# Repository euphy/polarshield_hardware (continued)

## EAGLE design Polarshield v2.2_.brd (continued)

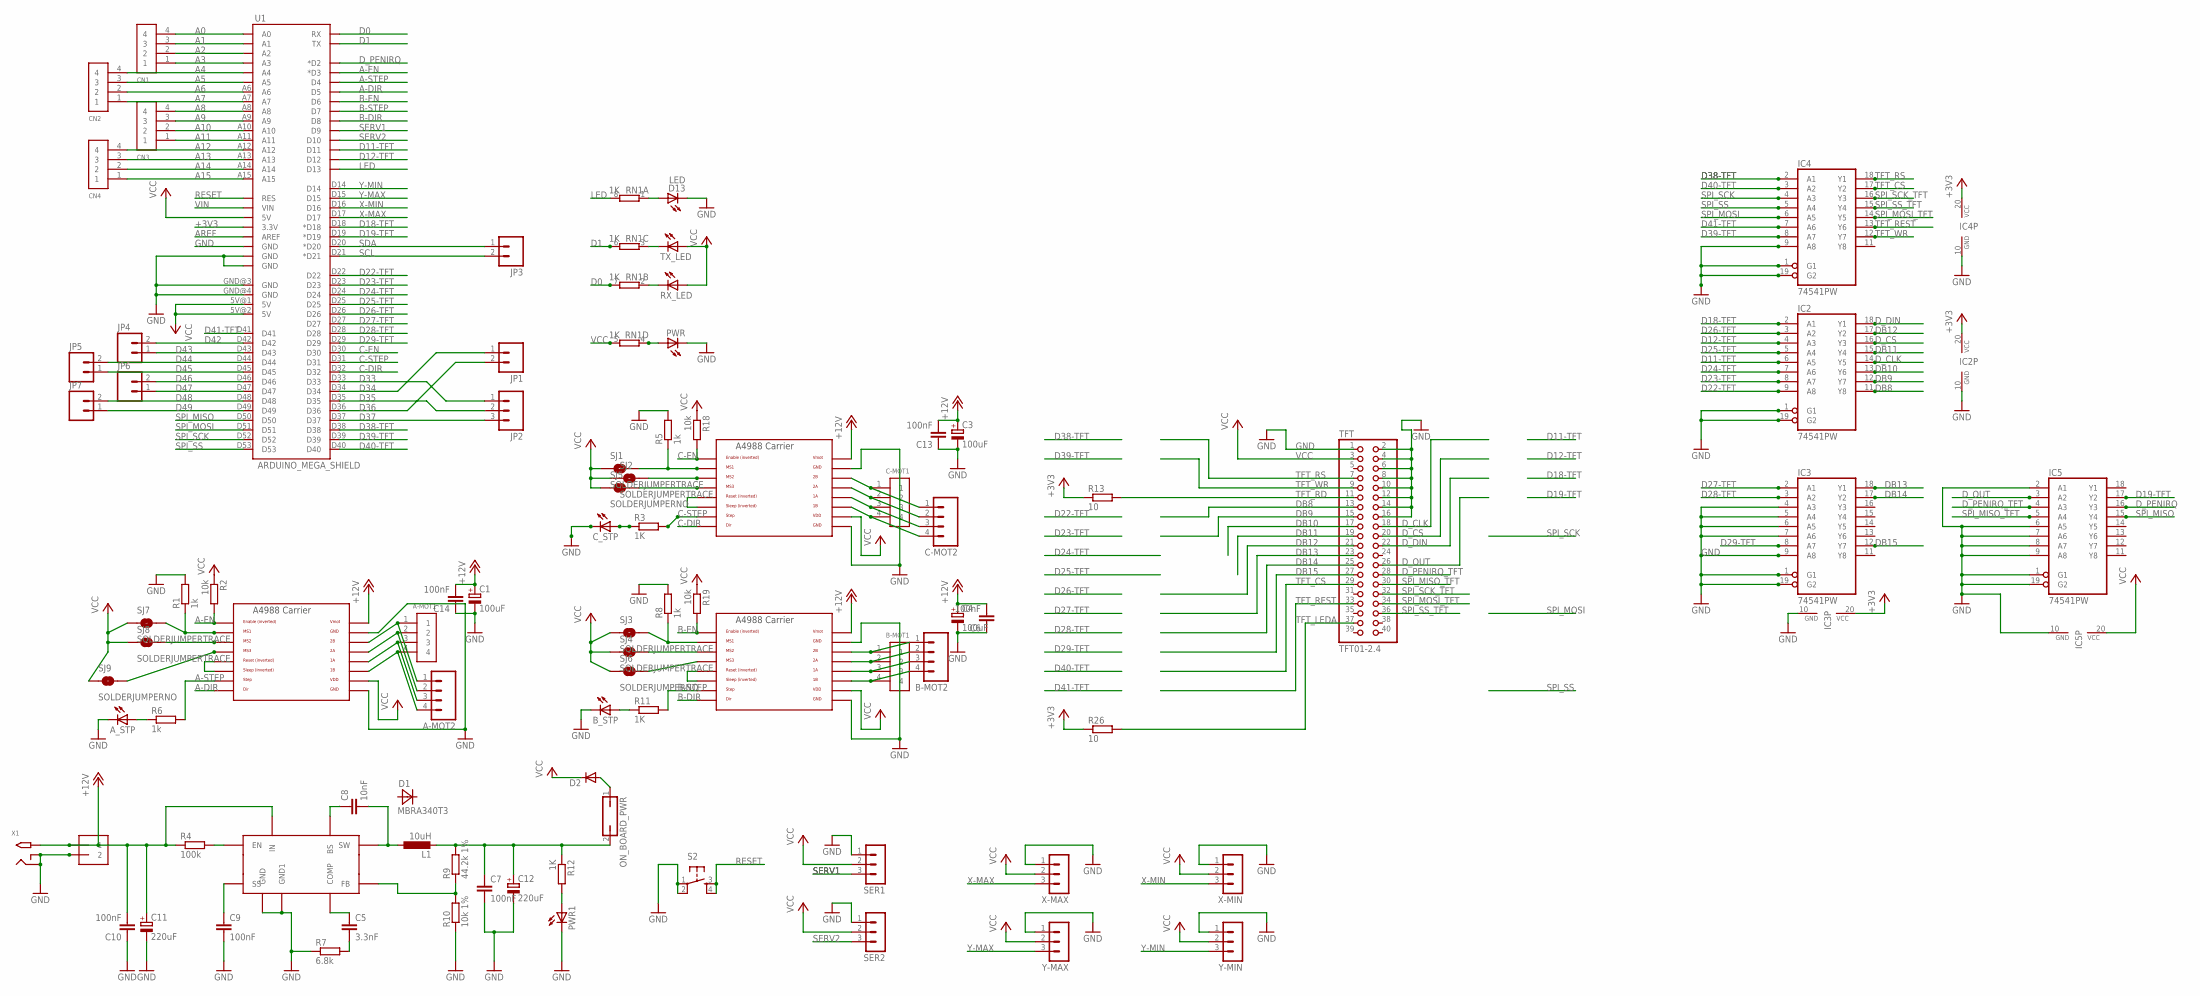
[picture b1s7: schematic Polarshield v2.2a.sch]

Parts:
A-MOT1: 1X4-BIG; 1X04-BIG
A-MOT2: M04SCREW; SCREWTERMINAL-3.5MM-4
A_STP: LEDCHIP-LED0805; CHIP-LED0805
B-MOT1: 1X4-BIG; 1X04-BIG
B-MOT2: M04SCREW; SCREWTERMINAL-3.5MM-4
B_STP: LEDCHIP-LED0805; CHIP-LED0805
C1, C3, C4: 100uF; 153CLV-0605
C5: 3.3nF; C0805K
C6, C13, C14: 100nF; C0805
C7, C9, C10: 100nF; C0805K
C8: 10nF; C0805K
C11, C12: 220uF; 153CLV-0807
C-MOT1: 1X4-BIG; 1X04-BIG
C-MOT2: M04SCREW; SCREWTERMINAL-3.5MM-4
CN1, CN2, CN3, CN4: 1X4-CLEANBIG; 1X04-CLEANBIG
C_STP: LEDCHIP-LED0805; CHIP-LED0805
D1: MBRA340T3; SMA
D2: DIODE-DO214BA; DO214BA
D13: LED; CHIP-LED0805
IC1: MP2307; SOIC8
IC2, IC3, IC4, IC5: 74541PW; TSSOP20
J1: 1X2-3.5MM
JP1, JP3, JP4, JP5, JP6, JP7: M021X02_NO_SILK; 1X02_NO_SILK
JP2: M031X03_NO_SILK; 1X03_NO_SILK
L1: 10uH; PIS2816
ON_BOARD_PWR: JP1Q; JP1
PWR, PWR1: LEDCHIP-LED0805; CHIP-LED0805
R1, R5, R6, R8: 1k; R0805
R2, R18, R19: 10k; R0805
R3, R11, R12: 1K; R0805
R4: 100k; R0805
R7: 6.8k; R0805
R9: 44.2k 1%; R0805
R10: 10k 1%; R0805
R13, R26: 10; R0805
RN1: 1K; EXBS8V
RX_LED: LEDCHIP-LED0805; CHIP-LED0805
S2: TAC_SWITCHPTH; TACTILE-PTH
SER1, SER2: 3PIN-HEADER
SJ1, SJ2, SJ3, SJ4, SJ7, SJ8: SOLDERJUMPERTRACE; SJ_2S-TRACE
SJ5, SJ6, SJ9: SOLDERJUMPERNO; SJ_2S-NO
TFT: TFT01-2.4
TX_LED: LEDCHIP-LED0805; CHIP-LED0805
U1: ARDUINO_MEGA_SHIELD
U$1, U$6, U$7: A4988BREAKOUT
X1: 2.1MMJACKTHM; PJ-102A
X-MAX: 3PIN-HEADER
X-MIN: 3PIN-HEADER
Y-MAX: 3PIN-HEADER
Y-MIN: 3PIN-HEADER

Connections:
+12V: C1.+, C3.+, C4.+, C6.2, C10.2, C11.+, C13.2, C14.2, IC1.IN, J1.1, R4.1, U$1.VMOT, U$6.VMOT, U$7.VMOT, X1.TIP; also elsewhere on the board
A0: CN1.4, U1.A0
A1: CN1.3, U1.A1
A2: CN1.2, U1.A2
A3: CN1.1, U1.A3
A4: CN2.4, U1.A4
A5: CN2.3, U1.A5
A6: CN2.2, U1.A6
A7: CN2.1, U1.A7
A8: CN3.4, U1.A8
A9: CN3.3, U1.A9
A10: CN3.2, U1.A10
A11: CN3.1, U1.A11
A12: CN4.4, U1.A12
A13: CN4.3, U1.A13
A14: CN4.2, U1.A14
A15: CN4.1, U1.A15
A-DIR: U1.D5, U$1.DIR
A-EN: R2.2, U1.D3 (*D3), U$1.EN
A-STEP: R6.2, U1.D4, U$1.STEP
AREF: U1.AREF
B-DIR: U1.D8, U$7.DIR
B-EN: R19.2, U1.D6, U$7.EN
B-STEP: R11.2, U1.D7, U$7.STEP
C-DIR: U1.D32, U$6.DIR
C-EN: R18.2, U1.D30, U$6.EN
C-STEP: R3.2, U1.D31, U$6.STEP
D0: RN1.7 (2), U1.RX
D1: RN1.6 (2), U1.TX
D11-TFT: IC2.6 (A5), U1.D11
D12-TFT: IC2.4 (A3), U1.D12
D19-TFT: IC5.17 (Y2), U1.D19 (*D19); also elsewhere on the board
D22-TFT: IC2.9 (A8), U1.D22
D23-TFT: IC2.8 (A7), U1.D23
D24-TFT: IC2.7 (A6), U1.D24
D25-TFT: IC2.5 (A4), U1.D25
D26-TFT: IC2.3 (A2), U1.D26
D27-TFT: IC3.2 (A1), U1.D27
D28-TFT: IC3.3 (A2), U1.D28
D29-TFT: IC3.8 (A7), U1.D29
D33: JP2.1, U1.D33
D34: JP1.1, U1.D34
D35: JP2.2, U1.D35
D36: JP1.2, U1.D36
D37: JP2.3, U1.D37
D38-TFT: IC4.2 (A1), U1.D38; also elsewhere on the board
D39-TFT: IC4.8 (A7), U1.D39; also elsewhere on the board
D40-TFT: IC4.3 (A2), U1.D40; also elsewhere on the board
D41-TFT: IC4.7 (A6), U1.D41; also elsewhere on the board
D42: JP4.2, U1.D42
D43: JP4.1, U1.D43
D44: JP5.2, U1.D44
D45: JP5.1, U1.D45
D46: JP6.2, U1.D46
D47: JP6.1, U1.D47
D48: JP7.2, U1.D48
D49: JP7.1, U1.D49
DB8: IC2.11 (Y8), TFT.13
DB9: IC2.12 (Y7), TFT.15
DB10: IC2.13 (Y6), TFT.17
DB11: IC2.15 (Y4), TFT.19
DB12: IC2.17 (Y2), TFT.21
DB13: IC3.18 (Y1), TFT.23
DB14: IC3.17 (Y2), TFT.25
DB15: IC3.12 (Y7), TFT.27
D_CLK: IC2.14 (Y5), TFT.18
D_CS: IC2.16 (Y3), TFT.20
D_DIN: IC2.18 (Y1), TFT.22; also elsewhere on the board
D_PENIRQ: IC5.16 (Y3), U1.D2 (*D2); also elsewhere on the board
LED: RN1.8 (2), U1.D13
unnamed: U$6.RST, U$6.SLP (SLEEP)
unnamed: PWR.A, RN1.4 (1)
unnamed: R5.1, SJ1.2, U$6.MS1
unnamed: A-MOT1.1, A-MOT2.1, U$1.2B
unnamed: A-MOT1.2, A-MOT2.2, U$1.2A
unnamed: A-MOT1.3, A-MOT2.3, U$1.1A
unnamed: A-MOT1.4, A-MOT2.4, U$1.1B
unnamed: U$1.RST, U$1.SLP (SLEEP)
unnamed: R1.1, SJ7.2, U$1.MS1
unnamed: SJ2.2, U$6.MS2
unnamed: SJ8.2, U$1.MS2
unnamed: SJ5.2, U$6.MS3
unnamed: U$7.RST, U$7.SLP (SLEEP)
unnamed: SJ9.2, U$1.MS3
unnamed: RN1.2 (1), RX_LED.C
unnamed: RN1.3 (1), TX_LED.C
unnamed: SJ4.2, U$7.MS2
unnamed: B_STP.A, R11.1
unnamed: A_STP.A, R6.1
unnamed: D13.A, RN1.1
unnamed: C-MOT1.1, C-MOT2.1, U$6.2B
unnamed: C-MOT1.2, C-MOT2.2, U$6.2A
unnamed: C_STP.A, R3.1
unnamed: PWR1.A, R12.2
unnamed: C-MOT1.3, C-MOT2.3, U$6.1A
unnamed: C-MOT1.4, C-MOT2.4, U$6.1B
unnamed: B-MOT1.1, B-MOT2.1, U$7.2B
unnamed: B-MOT1.2, B-MOT2.2, U$7.2A
unnamed: B-MOT1.3, B-MOT2.3, U$7.1A
unnamed: SJ6.2, U$7.MS3
unnamed 100: IC1.FB, R9.1, R10.2; also elsewhere on the board
unnamed: R8.1, SJ3.2, U$7.MS1
unnamed 102: IC1.EN, R4.2; also elsewhere on the board
unnamed: B-MOT1.4, B-MOT2.4, U$7.1B
unnamed 105: C9.1, IC1.SS; also elsewhere on the board
unnamed: C5.2, R7.2
unnamed 107: C5.1, IC1.COMP; also elsewhere on the board
unnamed 108: C8.1, IC1.BS; also elsewhere on the board
unnamed 109: C8.2, IC1.SW, L1.1; also elsewhere on the board
RESET: S2.3, S2.4, U1.RES
SCL: JP3.2, U1.D21 (*D21)
SDA: JP3.1, U1.D20 (*D20)
SERV1: SER1.3, U1.D9
SERV2: SER2.3, U1.D10
SPI_MISO: IC5.15 (Y4), U1.D50; also elsewhere on the board
SPI_MOSI: IC4.6 (A5), U1.D51; also elsewhere on the board
SPI_MOSI_TFT: IC4.14 (Y5), TFT.34; also elsewhere on the board
SPI_SCK: IC4.4 (A3), U1.D52; also elsewhere on the board
SPI_SCK_TFT: IC4.16 (Y3), TFT.32; also elsewhere on the board
SPI_SS: IC4.5 (A4), U1.D53; also elsewhere on the board
SPI_SS_TFT: IC4.15 (Y4), TFT.36; also elsewhere on the board
TFT_CS: IC4.17 (Y2), TFT.29; also elsewhere on the board
TFT_LEDA: R26.2, TFT.37
TFT_RD: R13.2, TFT.11
TFT_REST: IC4.13 (Y6), TFT.33; also elsewhere on the board
TFT_RS: IC4.18 (Y1), TFT.7; also elsewhere on the board
TFT_WR: IC4.12 (Y7), TFT.9; also elsewhere on the board
VIN: U1.VIN; also elsewhere on the board
X-MAX: U1.D17, X-MAX.3; also elsewhere on the board
X-MIN: U1.D16, X-MIN.3; also elsewhere on the board
Y-MAX: U1.D15, Y-MAX.3; also elsewhere on the board
Y-MIN: U1.D14, Y-MIN.3; also elsewhere on the board

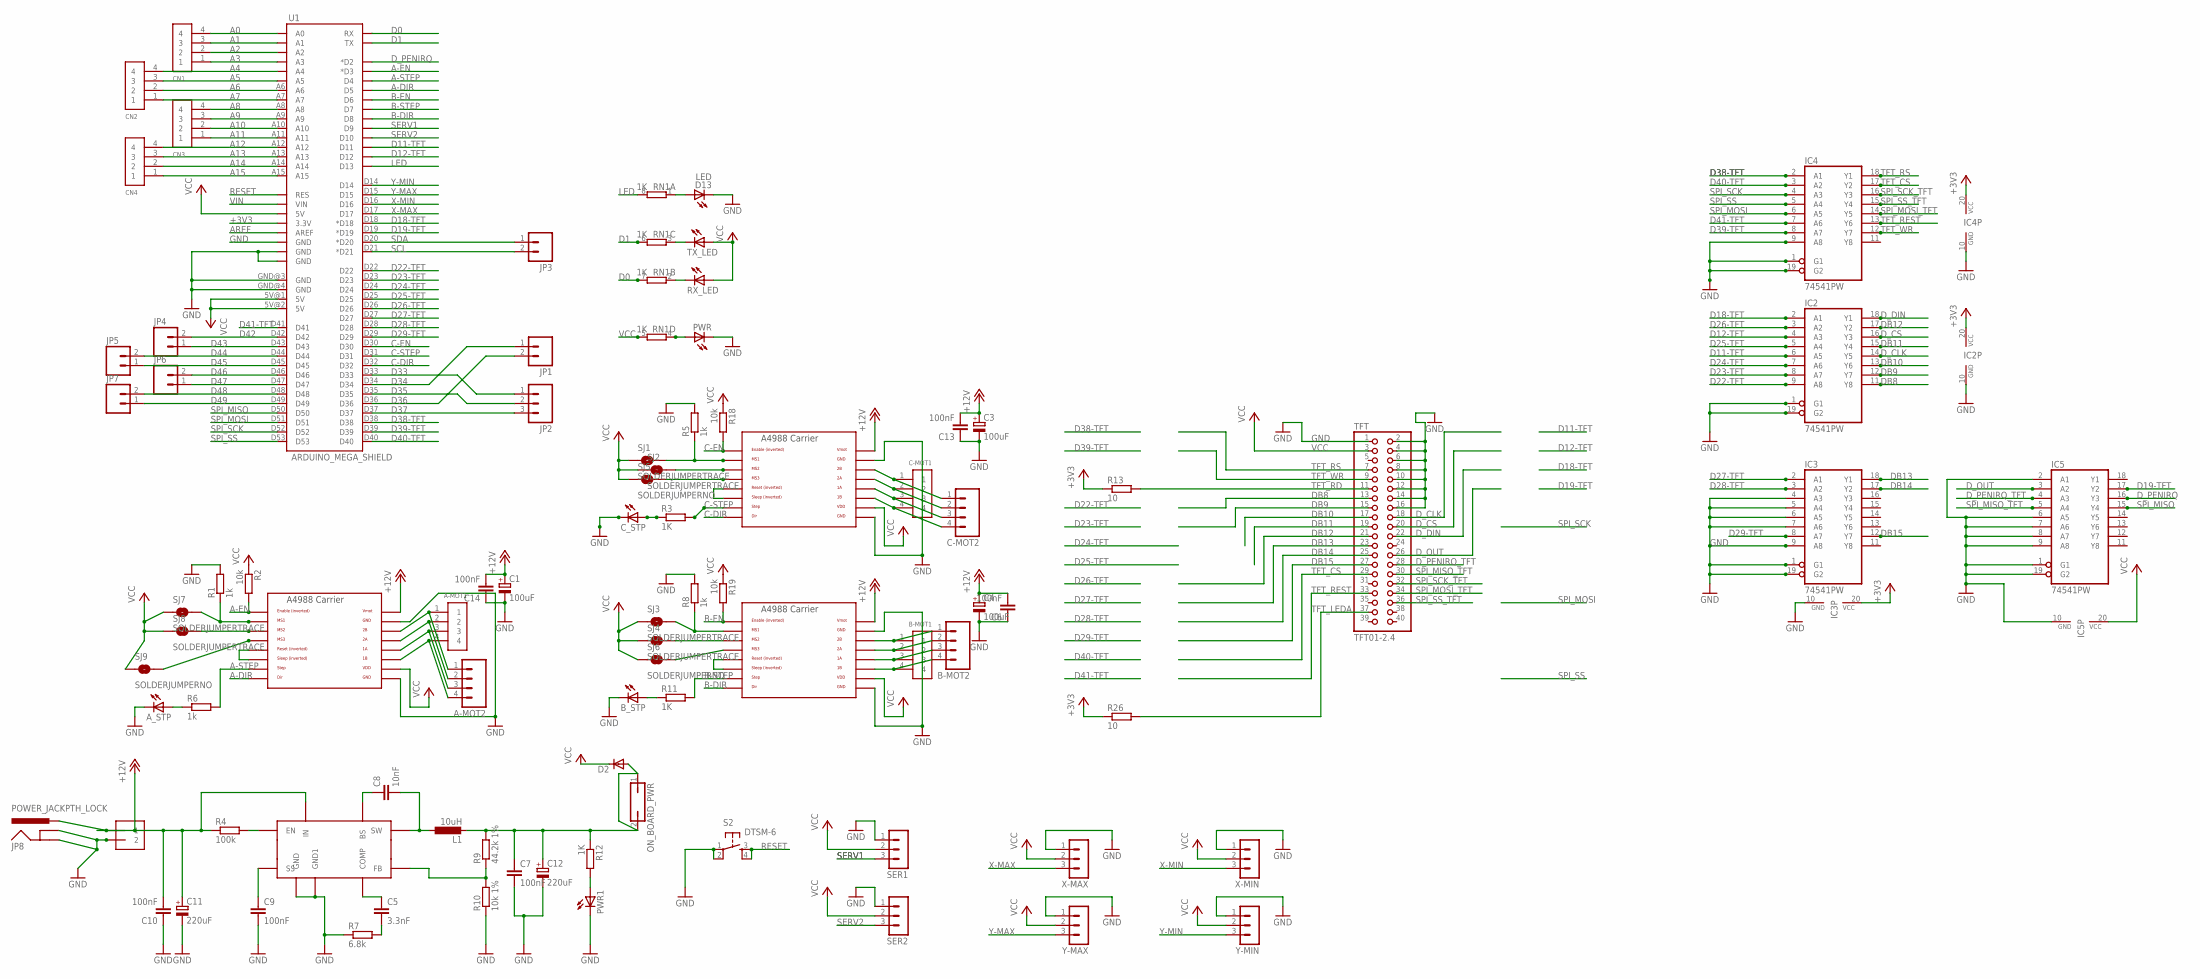
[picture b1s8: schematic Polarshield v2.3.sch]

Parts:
A-MOT1: 1X4-BIG; 1X04-BIG
A-MOT2: M04SCREW; SCREWTERMINAL-3.5MM-4
A_STP: LEDCHIP-LED0805; CHIP-LED0805
B-MOT1: 1X4-BIG; 1X04-BIG
B-MOT2: M04SCREW; SCREWTERMINAL-3.5MM-4
B_STP: LEDCHIP-LED0805; CHIP-LED0805
C1, C3, C4: 100uF; 153CLV-0605
C5: 3.3nF; C0805K
C6, C13, C14: 100nF; C0805
C7, C9, C10: 100nF; C0805K
C8: 10nF; C0805K
C11, C12: 220uF; 153CLV-0807
C-MOT1: 1X4-BIG; 1X04-BIG
C-MOT2: M04SCREW; SCREWTERMINAL-3.5MM-4
CN1, CN2, CN3, CN4: 1X4-CLEANBIG; 1X04-CLEANBIG
C_STP: LEDCHIP-LED0805; CHIP-LED0805
D2: DIODE-DO214BA; DO214BA
D13: LED; CHIP-LED0805
IC1: MP2307; SOIC8
IC2, IC3, IC4, IC5: 74541PW; TSSOP20
J1: 1X2-3.5MM
JP1, JP3, JP4, JP5, JP6, JP7: M021X02_NO_SILK; 1X02_NO_SILK
JP2: M031X03_NO_SILK; 1X03_NO_SILK
JP8: POWER_JACKPTH_LOCK; POWER_JACK_PTH_LOCK
L1: 10uH; PIS2816
ON_BOARD_PWR: JP1Q; JP1
PWR, PWR1: LEDCHIP-LED0805; CHIP-LED0805
R1, R5, R6, R8: 1k; R0805
R2, R18, R19: 10k; R0805
R3, R11, R12: 1K; R0805
R4: 100k; R0805
R7: 6.8k; R0805
R9: 44.2k 1%; R0805
R10: 10k 1%; R0805
R13, R26: 10; R0805
RN1: 1K; EXBS8V
RX_LED: LEDCHIP-LED0805; CHIP-LED0805
S2: DTSM-6
SER1, SER2: 3PIN-HEADER
SJ1, SJ2, SJ3, SJ4, SJ7, SJ8: SOLDERJUMPERTRACE; SJ_2S-TRACE
SJ5, SJ6, SJ9: SOLDERJUMPERNO; SJ_2S-NO
TFT: TFT01-2.4
TX_LED: LEDCHIP-LED0805; CHIP-LED0805
U1: ARDUINO_MEGA_SHIELD
U$1, U$6, U$7: A4988BREAKOUT
X-MAX: 3PIN-HEADER
X-MIN: 3PIN-HEADER
Y-MAX: 3PIN-HEADER
Y-MIN: 3PIN-HEADER

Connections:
+12V: C1.+, C3.+, C4.+, C6.2, C10.2, C11.+, C13.2, C14.2, IC1.IN, J1.1, JP8.PWR, R4.1, U$1.VMOT, U$6.VMOT, U$7.VMOT; also elsewhere on the board
A0: CN1.4, U1.A0
A1: CN1.3, U1.A1
A2: CN1.2, U1.A2
A3: CN1.1, U1.A3
A4: CN2.4, U1.A4
A5: CN2.3, U1.A5
A6: CN2.2, U1.A6
A7: CN2.1, U1.A7
A8: CN3.4, U1.A8
A9: CN3.3, U1.A9
A10: CN3.2, U1.A10
A11: CN3.1, U1.A11
A12: CN4.4, U1.A12
A13: CN4.3, U1.A13
A14: CN4.2, U1.A14
A15: CN4.1, U1.A15
A-DIR: U1.D5, U$1.DIR
A-EN: R2.2, U1.D3 (*D3), U$1.EN
A-STEP: R6.2, U1.D4, U$1.STEP
AREF: U1.AREF
B-DIR: U1.D8, U$7.DIR
B-EN: R19.2, U1.D6, U$7.EN
B-STEP: R11.2, U1.D7, U$7.STEP
C-DIR: U1.D32, U$6.DIR
C-EN: R18.2, U1.D30, U$6.EN
C-STEP: R3.2, U1.D31, U$6.STEP
D0: RN1.7 (2), U1.RX
D1: RN1.6 (2), U1.TX
D11-TFT: IC2.6 (A5), U1.D11
D12-TFT: IC2.4 (A3), U1.D12
D19-TFT: IC5.17 (Y2), U1.D19 (*D19); also elsewhere on the board
D22-TFT: IC2.9 (A8), U1.D22
D23-TFT: IC2.8 (A7), U1.D23
D24-TFT: IC2.7 (A6), U1.D24
D25-TFT: IC2.5 (A4), U1.D25
D26-TFT: IC2.3 (A2), U1.D26
D27-TFT: IC3.2 (A1), U1.D27
D28-TFT: IC3.3 (A2), U1.D28
D29-TFT: IC3.8 (A7), U1.D29
D33: JP2.1, U1.D33
D34: JP1.1, U1.D34
D35: JP2.2, U1.D35
D36: JP1.2, U1.D36
D37: JP2.3, U1.D37
D38-TFT: IC4.2 (A1), U1.D38; also elsewhere on the board
D39-TFT: IC4.8 (A7), U1.D39; also elsewhere on the board
D40-TFT: IC4.3 (A2), U1.D40; also elsewhere on the board
D41-TFT: IC4.7 (A6), U1.D41; also elsewhere on the board
D42: JP4.2, U1.D42
D43: JP4.1, U1.D43
D44: JP5.2, U1.D44
D45: JP5.1, U1.D45
D46: JP6.2, U1.D46
D47: JP6.1, U1.D47
D48: JP7.2, U1.D48
D49: JP7.1, U1.D49
DB8: IC2.11 (Y8), TFT.13
DB9: IC2.12 (Y7), TFT.15
DB10: IC2.13 (Y6), TFT.17
DB11: IC2.15 (Y4), TFT.19
DB12: IC2.17 (Y2), TFT.21
DB13: IC3.18 (Y1), TFT.23
DB14: IC3.17 (Y2), TFT.25
DB15: IC3.12 (Y7), TFT.27
D_CLK: IC2.14 (Y5), TFT.18
D_CS: IC2.16 (Y3), TFT.20
D_DIN: IC2.18 (Y1), TFT.22; also elsewhere on the board
D_PENIRQ: IC5.16 (Y3), U1.D2 (*D2); also elsewhere on the board
LED: RN1.8 (2), U1.D13
unnamed: U$6.RST, U$6.SLP (SLEEP)
unnamed: PWR.A, RN1.4 (1)
unnamed: R5.1, SJ1.2, U$6.MS1
unnamed: A-MOT1.1, A-MOT2.1, U$1.2B
unnamed: A-MOT1.2, A-MOT2.2, U$1.2A
unnamed: A-MOT1.3, A-MOT2.3, U$1.1A
unnamed: A-MOT1.4, A-MOT2.4, U$1.1B
unnamed: U$1.RST, U$1.SLP (SLEEP)
unnamed: R1.1, SJ7.2, U$1.MS1
unnamed: SJ2.2, U$6.MS2
unnamed: SJ8.2, U$1.MS2
unnamed: SJ5.2, U$6.MS3
unnamed: U$7.RST, U$7.SLP (SLEEP)
unnamed: SJ9.2, U$1.MS3
unnamed: RN1.2 (1), RX_LED.C
unnamed: RN1.3 (1), TX_LED.C
unnamed: SJ4.2, U$7.MS2
unnamed: B_STP.A, R11.1
unnamed: A_STP.A, R6.1
unnamed: D13.A, RN1.1
unnamed: C-MOT1.1, C-MOT2.1, U$6.2B
unnamed: C-MOT1.2, C-MOT2.2, U$6.2A
unnamed: C_STP.A, R3.1
unnamed: PWR1.A, R12.2
unnamed: C-MOT1.3, C-MOT2.3, U$6.1A
unnamed: C-MOT1.4, C-MOT2.4, U$6.1B
unnamed: B-MOT1.1, B-MOT2.1, U$7.2B
unnamed: B-MOT1.2, B-MOT2.2, U$7.2A
unnamed: B-MOT1.3, B-MOT2.3, U$7.1A
unnamed: SJ6.2, U$7.MS3
unnamed 100: IC1.FB, R9.1, R10.2; also elsewhere on the board
unnamed: R8.1, SJ3.2, U$7.MS1
unnamed 102: IC1.EN, R4.2; also elsewhere on the board
unnamed: B-MOT1.4, B-MOT2.4, U$7.1B
unnamed 105: C9.1, IC1.SS; also elsewhere on the board
unnamed: C5.2, R7.2
unnamed 107: C5.1, IC1.COMP; also elsewhere on the board
unnamed 108: C8.1, IC1.BS; also elsewhere on the board
unnamed 109: C8.2, IC1.SW, L1.1; also elsewhere on the board
RESET: S2.3, S2.4, U1.RES
SCL: JP3.2, U1.D21 (*D21)
SDA: JP3.1, U1.D20 (*D20)
SERV1: SER1.3, U1.D9
SERV2: SER2.3, U1.D10
SPI_MISO: IC5.15 (Y4), U1.D50; also elsewhere on the board
SPI_MOSI: IC4.6 (A5), U1.D51; also elsewhere on the board
SPI_MOSI_TFT: IC4.14 (Y5), TFT.34; also elsewhere on the board
SPI_SCK: IC4.4 (A3), U1.D52; also elsewhere on the board
SPI_SCK_TFT: IC4.16 (Y3), TFT.32; also elsewhere on the board
SPI_SS: IC4.5 (A4), U1.D53; also elsewhere on the board
SPI_SS_TFT: IC4.15 (Y4), TFT.36; also elsewhere on the board
TFT_CS: IC4.17 (Y2), TFT.29; also elsewhere on the board
TFT_LEDA: R26.2, TFT.37
TFT_RD: R13.2, TFT.11
TFT_REST: IC4.13 (Y6), TFT.33; also elsewhere on the board
TFT_RS: IC4.18 (Y1), TFT.7; also elsewhere on the board
TFT_WR: IC4.12 (Y7), TFT.9; also elsewhere on the board
VIN: U1.VIN; also elsewhere on the board
X-MAX: U1.D17, X-MAX.3; also elsewhere on the board
X-MIN: U1.D16, X-MIN.3; also elsewhere on the board
Y-MAX: U1.D15, Y-MAX.3; also elsewhere on the board
Y-MIN: U1.D14, Y-MIN.3; also elsewhere on the board

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
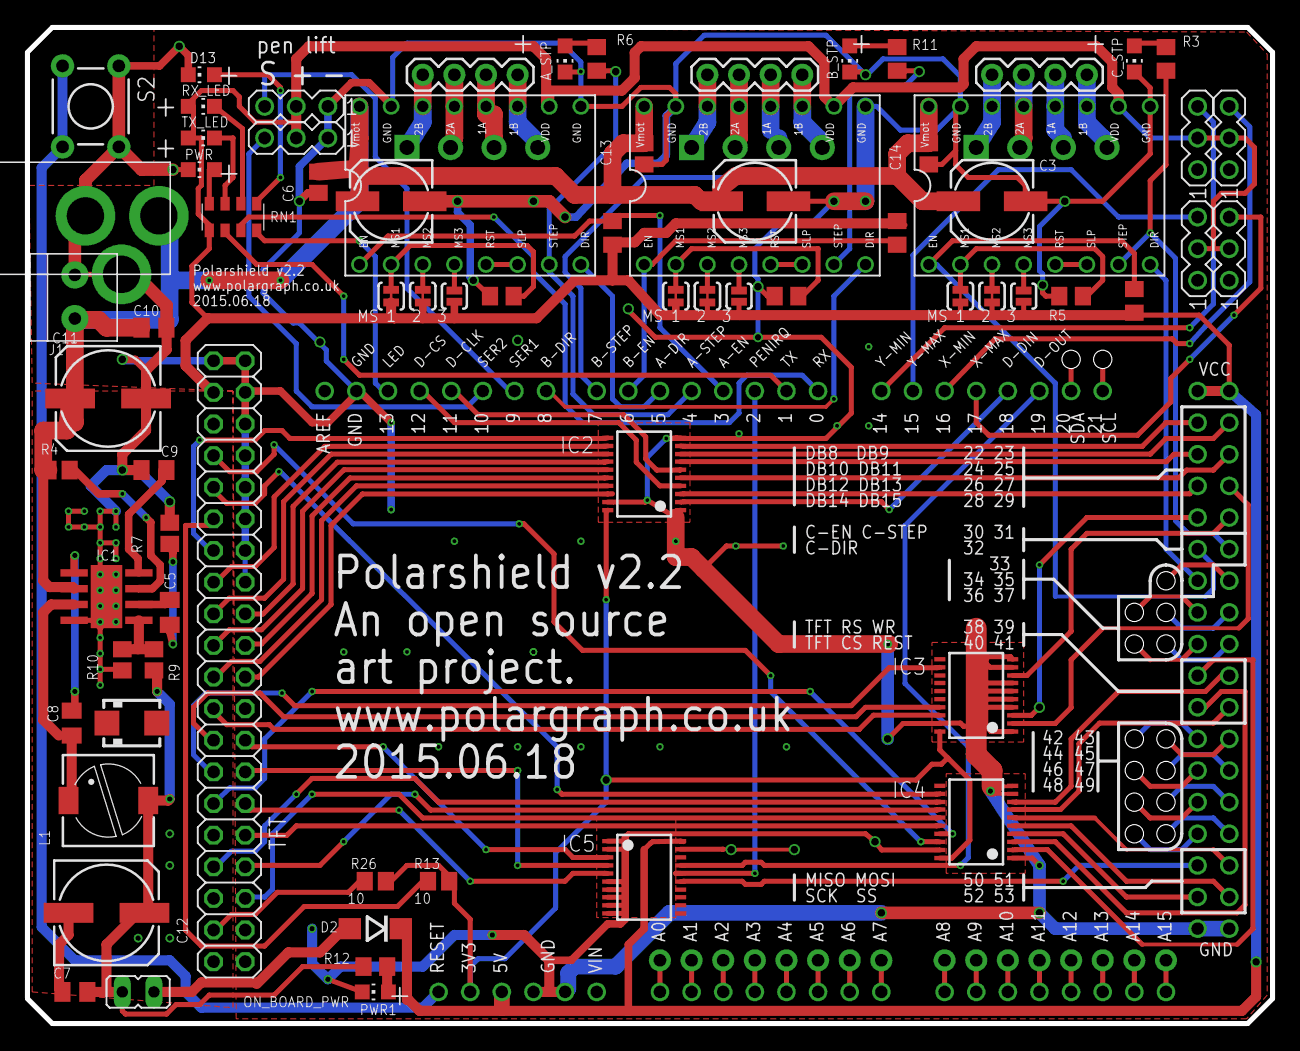
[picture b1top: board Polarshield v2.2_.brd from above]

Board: 4 copper layers, 100.0 x 80.0 mm, 87 parts (0 on the bottom side), 139 nets.

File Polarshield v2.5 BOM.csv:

Part/Designator,Manufacture Part Number/Seeed SKU,Quantity,,value,package,description
"RN1, RN2",301030012,2,,,,Array Chip Resistor
"IC2, IC3, IC4, IC5",74541PW,2,,,TSSOP20,"Octal BUFFER and LINE DRIVER, 3-state"
"C6, C7, C9, C10, C13",C-EUC0805,5,,100nF,C0805,"CAPACITOR, European symbol"
C5,C-EUC0805K,1,,3.3nF,C0805K,"CAPACITOR, European symbol"
C8,C-EUC0805K,1,,10nF,C0805K,"CAPACITOR, European symbol"
"C1, C4",153CLV-0605,2,,100uF,153CLV-0605,"POLARIZED CAPACITOR, European symbol"
"C11, C12",302030053,2,,220uF,153CLV-0807,"POLARIZED CAPACITOR, European symbol"
D2,DIODE-DO214BA,1,,,DO214BA,DIODE
S1,DTSM-6,1,,,DTSM-6,TACTILE BUTTON
"A_STP, B_STP, D13, PWR, PWR1, RX_LED, TX_LED",304090039,7,,yellow,CHIP-LED0805,LED
L1,303010016,1,,1uH,PIS2816,"INDUCTOR, European symbol"
IC1,MP2307,1,,,SOIC8,
"R2, R19",301010299,2,,10k,R0805,"RESISTOR, European symbol"
R4,301010089,1,,100k,R0805,"RESISTOR, European symbol"
R7,301010198,1,,6.8k,R0805,"RESISTOR, European symbol"
R9,R0807,1,,44.2k 1%,R0805,"RESISTOR, European symbol"
R10,301010299,1,,10k 1%,R0805,"RESISTOR, European symbol"
R12,301010311,1,,1K,R0805,"RESISTOR, European symbol"
"R13, R26",301010096,2,,10,R0805,"RESISTOR, European symbol"

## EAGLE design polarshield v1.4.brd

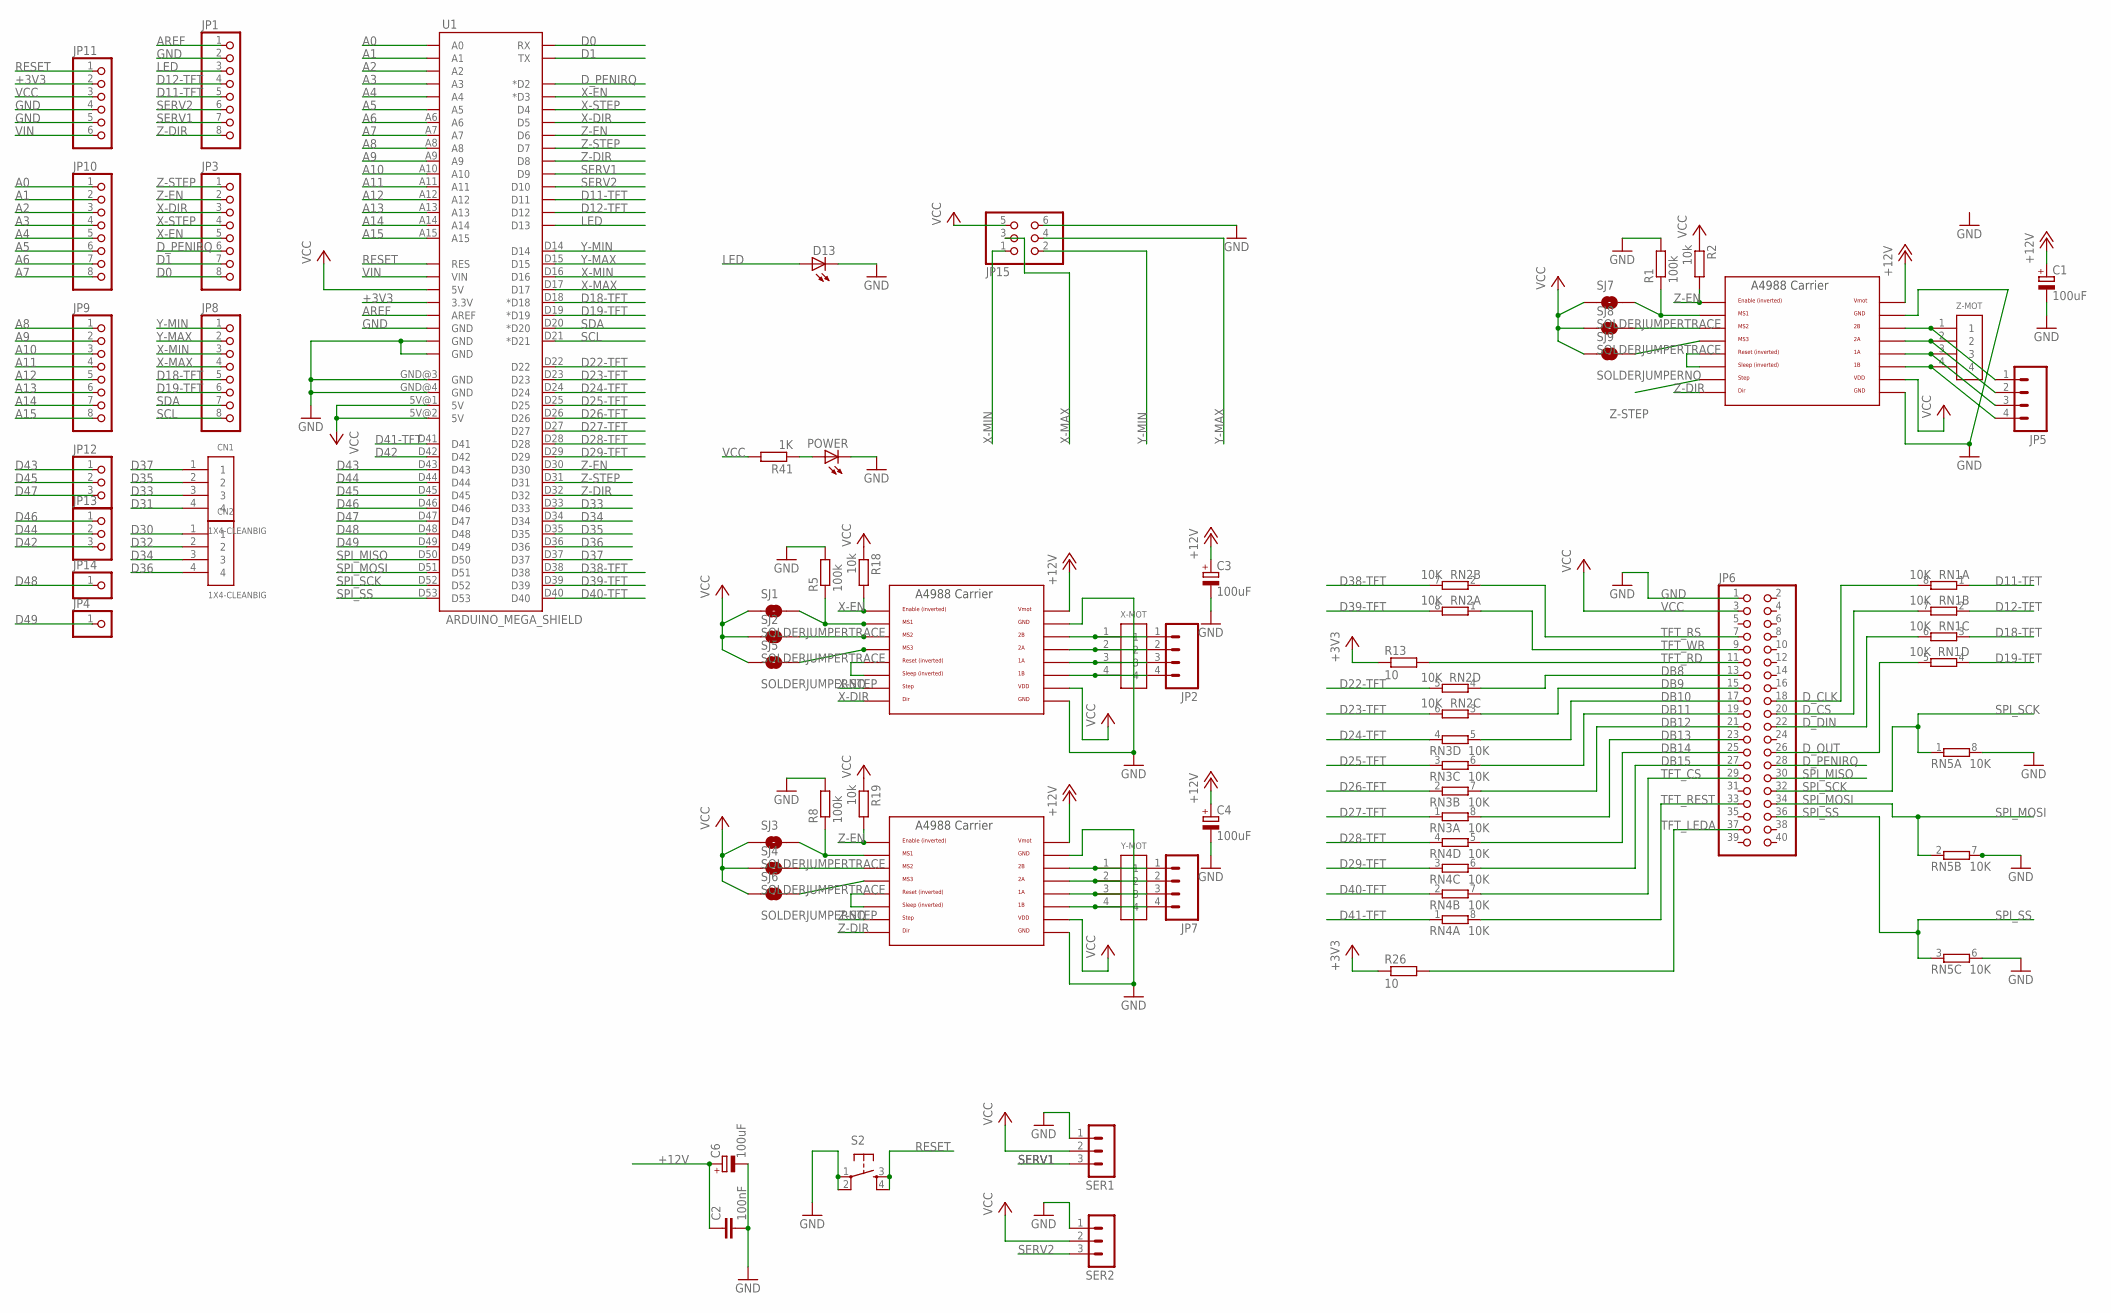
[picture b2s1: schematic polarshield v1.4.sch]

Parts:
C1, C3, C4, C6: 100uF; 153CLV-0605
C2: 100nF; C0805
CN1, CN2: 1X4-CLEANBIG; 1X04-CLEANBIG
D13: LEDCHIP-LED0805; CHIP-LED0805
JP1, JP3, JP8, JP9, JP10: PINHD-1X8CLEANBIG; 1X08-CLEANBIG
JP2, JP5, JP7: M04SCREW; SCREWTERMINAL-3.5MM-4
JP4, JP14: PINHD-1X1CB; 1X01-CLEANBIG
JP6: PINHD-2X20; 2X20
JP11: PINHD-1X6CB; 1X06-CLEANBIG
JP12, JP13: PINHD-1X3CB; 1X03-CLEANBIG
JP15: PINHD-2X3; 2X03
POWER: LEDCHIP-LED0805; CHIP-LED0805
R1, R5, R8: 100k; R0805
R2, R18, R19: 10k; R0805
R13, R26: 10; R0805
R41: 1K; R0805
RN1, RN2, RN3, RN4, RN5: 10K; EXBS8V
S2: TAC_SWITCHPTH; TACTILE-PTH
SER1, SER2: 3PIN-HEADER
SJ1, SJ2, SJ3, SJ4, SJ7, SJ8: SOLDERJUMPERTRACE; SJ_2S-TRACE
SJ5, SJ6, SJ9: SOLDERJUMPERNO; SJ_2S-NO
U1: ARDUINO_MEGA_SHIELD
U$1, U$6, U$7: A4988BREAKOUT
X-MOT: 1X4-BIG; 1X04-BIG
Y-MOT: 1X4-BIG; 1X04-BIG
Z-MOT: 1X4-BIG; 1X04-BIG

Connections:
+3V3: JP11.2, R13.1, R26.1, U1.3.3V
+12V: C1.+, C2.1, C3.+, C4.+, C6.+, U$1.VMOT, U$6.VMOT, U$7.VMOT
A0: JP10.1, U1.A0
A1: JP10.2, U1.A1
A2: JP10.3, U1.A2
A3: JP10.4, U1.A3
A4: JP10.5, U1.A4
A5: JP10.6, U1.A5
A6: JP10.7, U1.A6
A7: JP10.8, U1.A7
A8: JP9.1, U1.A8
A9: JP9.2, U1.A9
A10: JP9.3, U1.A10
A11: JP9.4, U1.A11
A12: JP9.5, U1.A12
A13: JP9.6, U1.A13
A14: JP9.7, U1.A14
A15: JP9.8, U1.A15
AREF: JP1.1, U1.AREF
D0: JP3.8, U1.RX
D1: JP3.7, U1.TX
D11-TFT: JP1.5, RN1.1, U1.D11
D12-TFT: JP1.4, RN1.2 (1), U1.D12
D18-TFT: JP8.5, RN1.3 (1), U1.D18 (*D18)
D19-TFT: JP8.6, RN1.4 (1), U1.D19 (*D19)
D22-TFT: RN2.5 (2), U1.D22
D23-TFT: RN2.6 (2), U1.D23
D24-TFT: RN3.4 (1), U1.D24
D25-TFT: RN3.3 (1), U1.D25
D26-TFT: RN3.2 (1), U1.D26
D27-TFT: RN3.1, U1.D27
D28-TFT: RN4.4 (1), U1.D28
D29-TFT: RN4.3 (1), U1.D29
D30: CN2.1
D31: CN1.4
D32: CN2.2
D33: CN1.3, U1.D33
D34: CN2.3, U1.D34
D35: CN1.2, U1.D35
D36: CN2.4, U1.D36
D37: CN1.1, U1.D37
D38-TFT: RN2.7 (2), U1.D38
D39-TFT: RN2.8 (2), U1.D39
D40-TFT: RN4.2 (1), U1.D40
D41-TFT: RN4.1, U1.D41
D42: JP13.3, U1.D42
D43: JP12.1, U1.D43
D44: JP13.2, U1.D44
D45: JP12.2, U1.D45
D46: JP13.1, U1.D46
D47: JP12.3, U1.D47
D48: JP14.1, U1.D48
D49: JP4.1, U1.D49
DB8: JP6.13, RN2.4 (1)
DB9: JP6.15, RN2.3 (1)
DB10: JP6.17, RN3.5 (2)
DB11: JP6.19, RN3.6 (2)
DB12: JP6.21, RN3.7 (2)
DB13: JP6.23, RN3.8 (2)
DB14: JP6.25, RN4.5 (2)
DB15: JP6.27, RN4.6 (2)
D_CLK: JP6.18, RN1.8 (2)
D_CS: JP6.20, RN1.7 (2)
D_DIN: JP6.22, RN1.6 (2)
D_OUT: JP6.26, RN1.5 (2)
D_PENIRQ: JP3.6, JP6.28, U1.D2 (*D2)
GND: C1.-, C2.2, C3.-, C4.-, C6.-, D13.C, JP1.2, JP6.1, JP11.4, JP11.5, JP15.6, POWER.C, R1.2, R5.2, R8.2, RN5.6 (2), RN5.7 (2), RN5.8 (2), S2.1, S2.2, SER1.1, SER2.1, U1.GND@0 (GND), U1.GND@1 (GND), U1.GND@2 (GND), U1.GND@3 (GND), U1.GND@4 (GND), U$1.GND, U$1.GND@0 (GND), U$6.GND, U$6.GND@0 (GND), U$7.GND, U$7.GND@0 (GND)
LED: D13.A, JP1.3, U1.D13
unnamed: U$6.RST, U$6.SLP (SLEEP)
unnamed: POWER.A, R41.1
unnamed: R5.1, SJ1.2, U$6.MS1
unnamed: SJ8.2, U$1.MS2
unnamed: SJ9.2, U$1.MS3
unnamed: R1.1, SJ7.2, U$1.MS1
unnamed: JP5.1, U$1.2B, Z-MOT.1
unnamed: JP5.2, U$1.2A, Z-MOT.2
unnamed: JP5.3, U$1.1A, Z-MOT.3
unnamed: SJ2.2, U$6.MS2
unnamed: JP5.4, U$1.1B, Z-MOT.4
unnamed: SJ5.2, U$6.MS3
unnamed: U$7.RST, U$7.SLP (SLEEP)
unnamed: U$1.RST, U$1.SLP (SLEEP)
unnamed: SJ4.2, U$7.MS2
unnamed: JP2.1, U$6.2B, X-MOT.1
unnamed: JP2.2, U$6.2A, X-MOT.2
unnamed: JP2.3, U$6.1A, X-MOT.3
unnamed: JP2.4, U$6.1B, X-MOT.4
unnamed: JP7.1, U$7.2B, Y-MOT.1
unnamed: JP7.2, U$7.2A, Y-MOT.2
unnamed: JP7.3, U$7.1A, Y-MOT.3
unnamed: SJ6.2, U$7.MS3
unnamed: R8.1, SJ3.2, U$7.MS1
unnamed: JP7.4, U$7.1B, Y-MOT.4
RESET: JP11.1, S2.3, S2.4, U1.RES
SCL: JP8.8, U1.D21 (*D21)
SDA: JP8.7, U1.D20 (*D20)
SERV1: JP1.7, SER1.3, U1.D9
SERV2: JP1.6, SER2.3, U1.D10
SPI_MISO: JP6.30, U1.D50
SPI_MOSI: JP6.34, RN5.2 (1), U1.D51
SPI_SCK: JP6.32, RN5.1, U1.D52
SPI_SS: JP6.36, RN5.3 (1), U1.D53
TFT_CS: JP6.29, RN4.7 (2)
TFT_LEDA: JP6.37, R26.2
TFT_RD: JP6.11, R13.2
TFT_REST: JP6.33, RN4.8 (2)
TFT_RS: JP6.7, RN2.2 (1)
TFT_WR: JP6.9, RN2.1
VCC: JP6.3, JP11.3, JP15.5, R2.1, R18.1, R19.1, R41.2, SER1.2, SER2.2, SJ1.1, SJ2.1, SJ3.1, SJ4.1, SJ5.1, SJ6.1, SJ7.1, SJ8.1, SJ9.1, U1.5V@0 (5V), U1.5V@1 (5V), U1.5V@2 (5V), U$1.VDD, U$6.VDD, U$7.VDD
VIN: JP11.6, U1.VIN
X-DIR: JP3.3, U1.D5, U$6.DIR
X-EN: JP3.5, R18.2, U1.D3 (*D3), U$6.EN
X-MAX: JP8.4, JP15.3, U1.D17
X-MIN: JP8.3, JP15.1, U1.D16
X-STEP: JP3.4, U1.D4, U$6.STEP
Y-MAX: JP8.2, JP15.4, U1.D15
Y-MIN: JP8.1, JP15.2, U1.D14
Z-DIR: JP1.8, U1.D8, U1.D32, U$1.DIR, U$7.DIR
Z-EN: JP3.2, R2.2, R19.2, U1.D6, U1.D30, U$1.EN, U$7.EN
Z-STEP: JP3.1, U1.D7, U1.D31, U$1.STEP, U$7.STEP

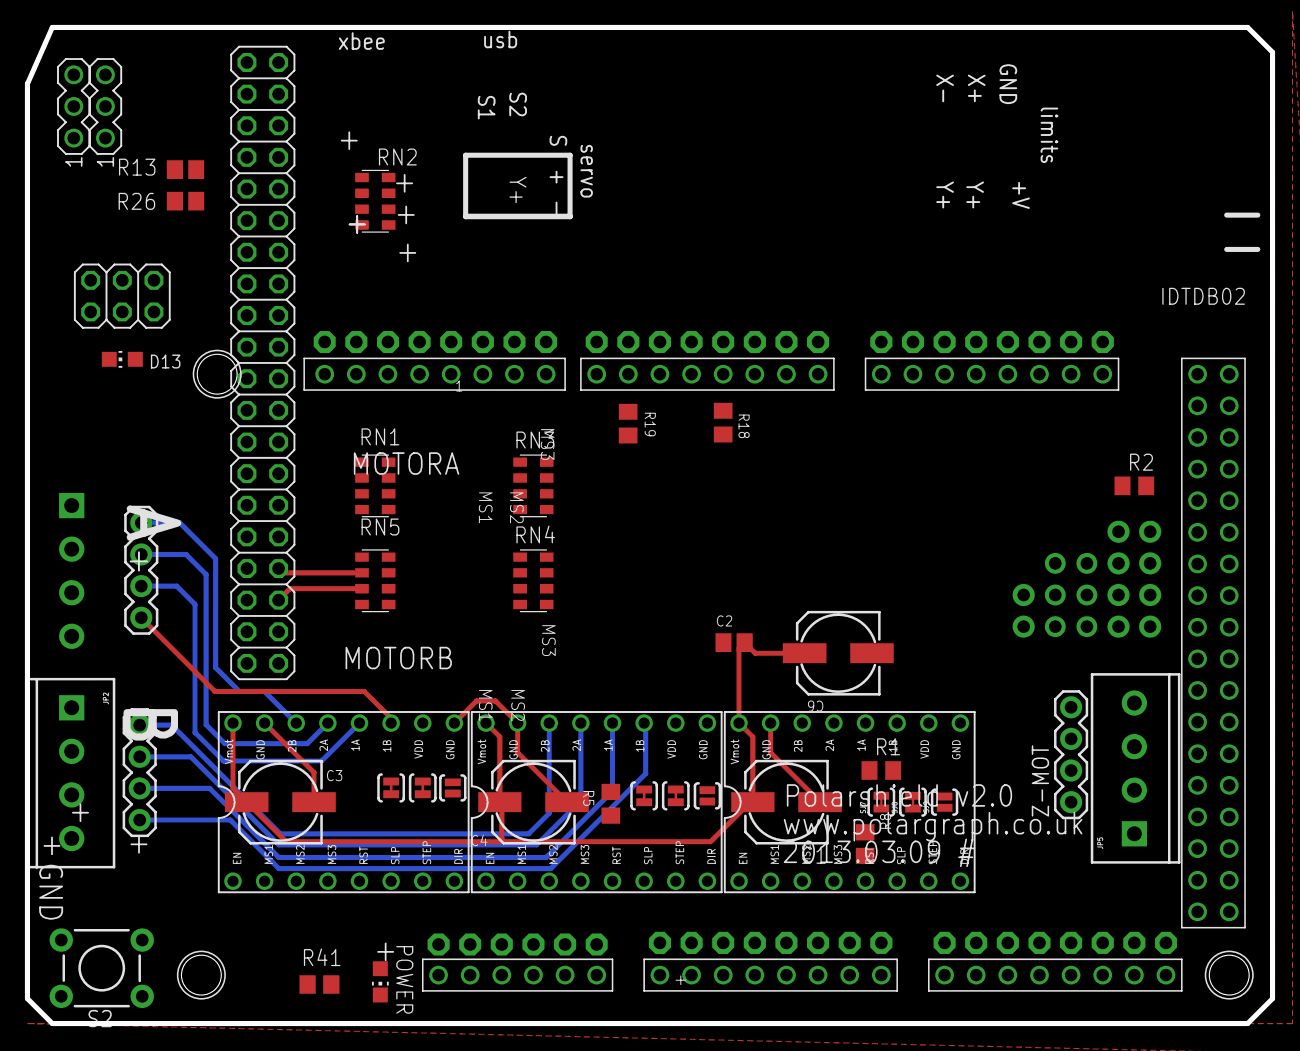
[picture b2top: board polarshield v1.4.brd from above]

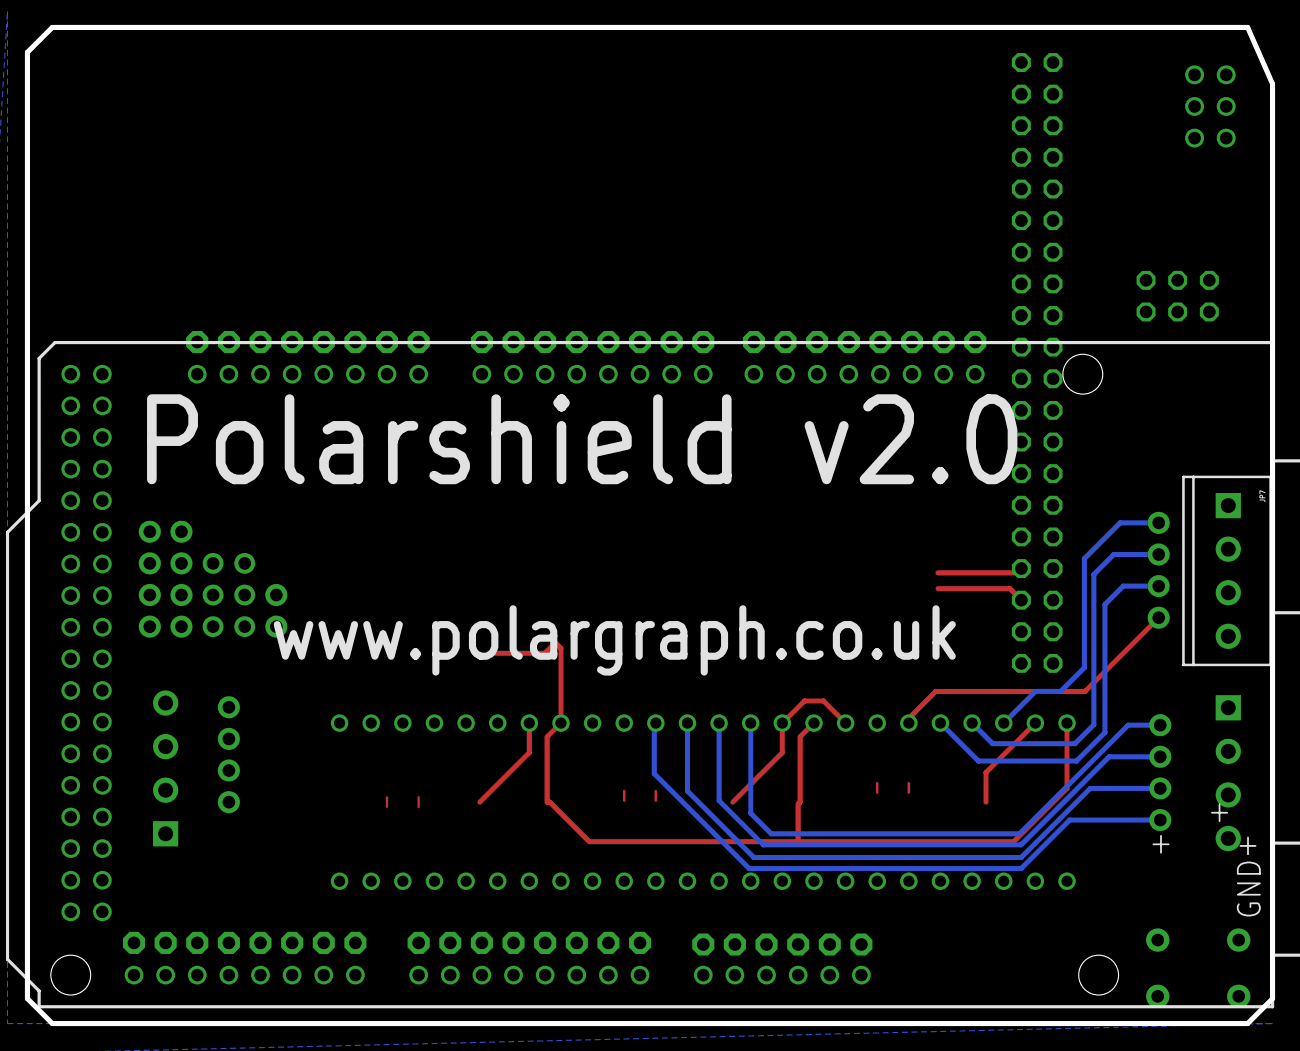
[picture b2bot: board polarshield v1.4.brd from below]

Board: 2 copper layers, 100.0 x 80.0 mm, 57 parts (3 on the bottom side), 117 nets.
